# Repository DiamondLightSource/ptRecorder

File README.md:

# ptRecorder
Pressure and Temperature recorder created by Daniel Brennand and comissioned by DLS Vacuum Dept.

### DLS Contacts

- Hugo Shiers
- Giles Knap

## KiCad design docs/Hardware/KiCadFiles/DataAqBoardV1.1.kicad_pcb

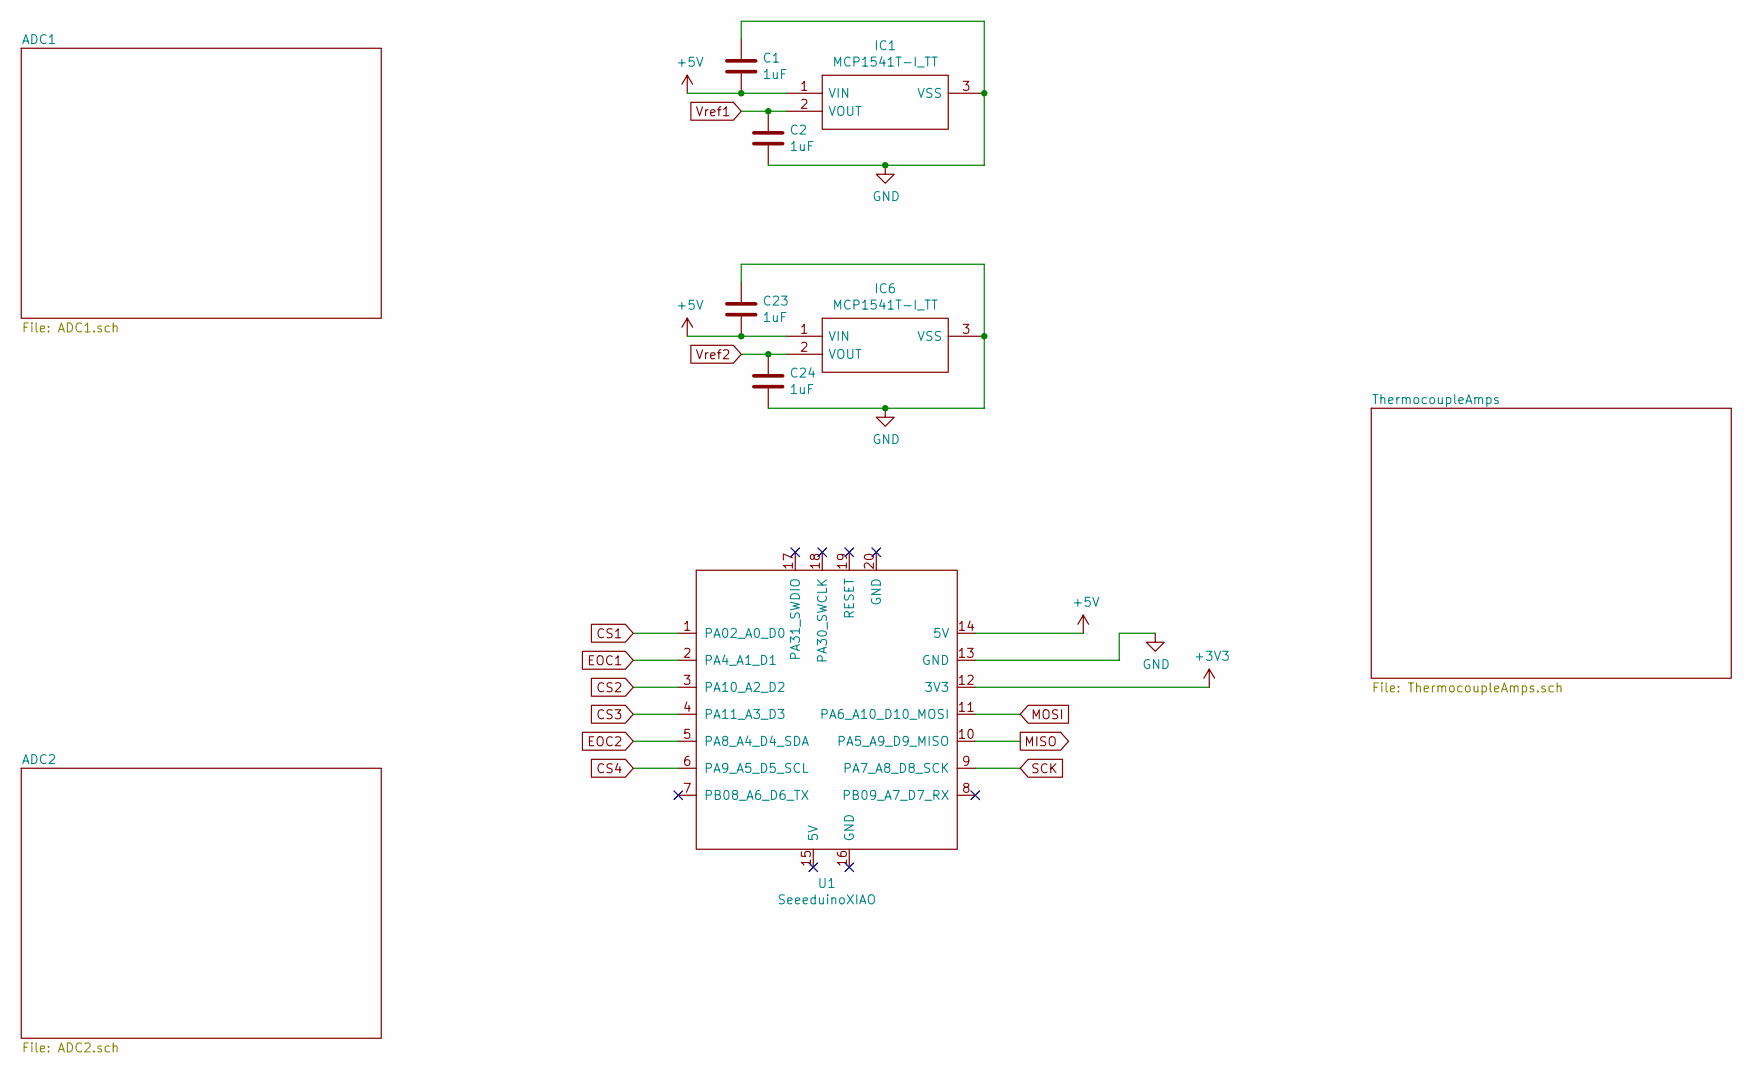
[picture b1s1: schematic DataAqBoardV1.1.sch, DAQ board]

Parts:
C1, C2, C23, C24: 1uF; C_0201_0603Metric
IC1, IC6: MCP1541T-I_TT; SOT96P237X112-3N; Manufacturer_Part_Number MCP1541T-I/TT
U1: SeeeduinoXIAO; Seeeduino XIAO-MOUDLE14P-2.54-21X17.8MM

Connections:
+3V3: U1.12 (3V3); also elsewhere on the board
+5V: C1.2, C23.2, IC1.1 (VIN), IC6.1 (VIN), U1.14 (5V); also elsewhere on the board
CS1: U1.1 (PA02_A0_D0); also elsewhere on the board
CS2: U1.3 (PA10_A2_D2); also elsewhere on the board
CS3: U1.4 (PA11_A3_D3); also elsewhere on the board
CS4: U1.6 (PA9_A5_D5_SCL); also elsewhere on the board
EOC1: U1.2 (PA4_A1_D1); also elsewhere on the board
EOC2: U1.5 (PA8_A4_D4_SDA); also elsewhere on the board
GND: C1.1, C2.2, C23.1, C24.2, IC1.3 (VSS), IC6.3 (VSS), U1.13 (GND); also elsewhere on the board
MISO: U1.10 (PA5_A9_D9_MISO); also elsewhere on the board
MOSI: U1.11 (PA6_A10_D10_MOSI); also elsewhere on the board
SCK: U1.9 (PA7_A8_D8_SCK); also elsewhere on the board
Vref1: C2.1, IC1.2 (VOUT); also elsewhere on the board
Vref2: C24.1, IC6.2 (VOUT); also elsewhere on the board

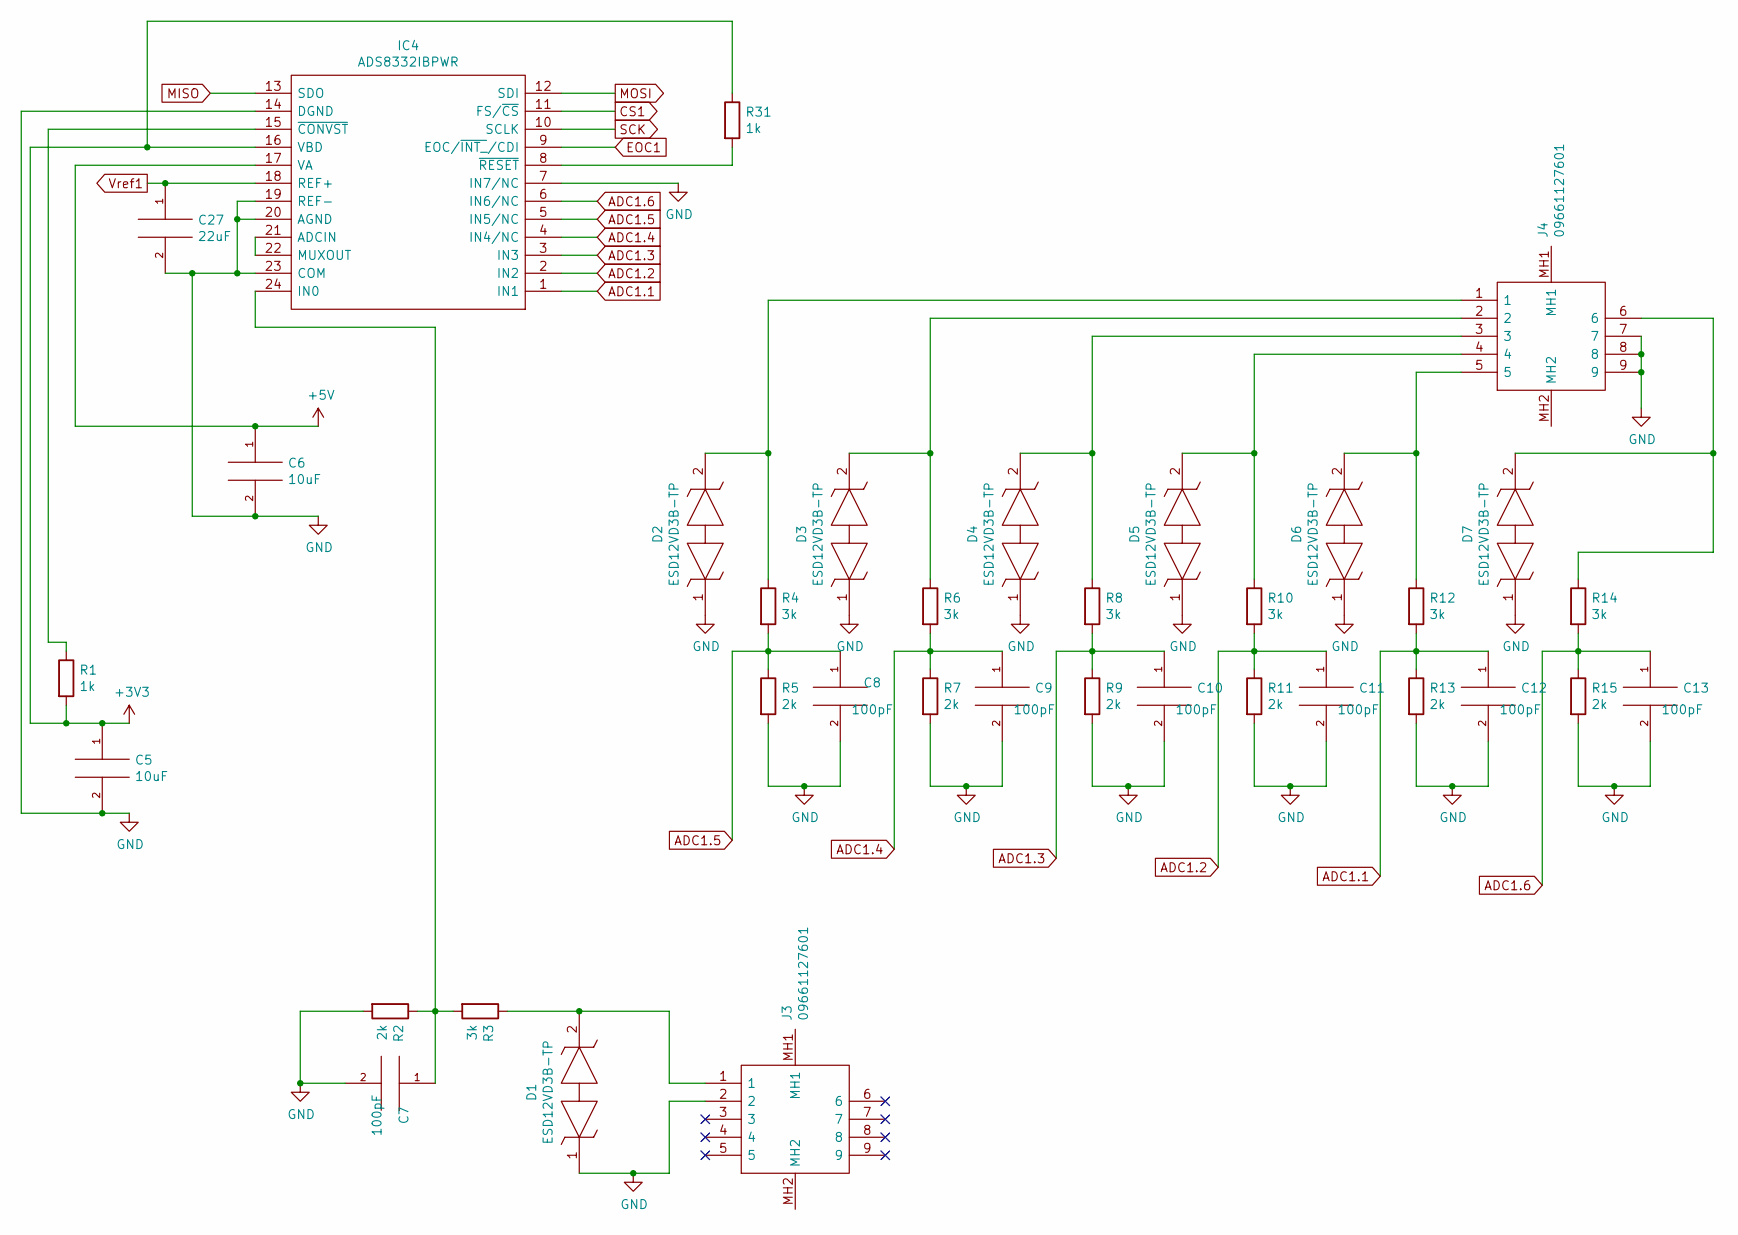
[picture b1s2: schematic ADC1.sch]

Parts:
C5, C6: 10uF; C_0201_0603Metric
C7, C8, C9, C10, C11, C12, C13: 100pF; C_0201_0603Metric
C27: 22uF; C_0201_0603Metric
D1, D2, D3, D4, D5, D6, D7: ESD12VD3B-TP; SOD2512X115N; Manufacturer_Part_Number ESD12VD3B-TP
IC4: ADS8332IBPWR; SOP65P640X120-24N; Manufacturer_Part_Number ADS8332IBPWR
J3, J4: 09661127601; 09661126600; Manufacturer_Part_Number 09661127601
R1, R31: 1k; R_0201_0603Metric
R2, R5, R7, R9, R11, R13, R15: 2k; R_0201_0603Metric
R3, R4, R6, R8, R10, R12, R14: 3k; R_0201_0603Metric

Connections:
+3V3: C5.1, IC4.16 (VBD), R1.2, R31.1; also elsewhere on the board
+5V: C6.1, IC4.17 (VA); also elsewhere on the board
ADC1.1: C12.1, IC4.1 (IN1), R12.2, R13.1
ADC1.2: C11.1, IC4.2 (IN2), R10.2, R11.1
ADC1.3: C10.1, IC4.3 (IN3), R8.2, R9.1
ADC1.4: C9.1, IC4.4 (IN4/NC), R6.2, R7.1
ADC1.5: C8.1, IC4.5 (IN5/NC), R4.2, R5.1
ADC1.6: C13.1, IC4.6 (IN6/NC), R14.2, R15.1
CS1: IC4.11 (FS/~CS); also elsewhere on the board
EOC1: IC4.9 (EOC/~INT_~/CDI); also elsewhere on the board
GND: C5.2, C6.2, C7.2, C8.2, C9.2, C10.2, C11.2, C12.2, C13.2, C27.2, D1.1, D2.1, D3.1, D4.1, D5.1, D6.1, D7.1, IC4.7 (IN7/NC), IC4.14 (DGND), IC4.19 (REF-), IC4.20 (AGND), IC4.23 (COM), J3.2, J4.7, J4.8, J4.9, R2.2, R5.2, R7.2, R9.2, R11.2, R13.2, R15.2; also elsewhere on the board
MISO: IC4.13 (SDO); also elsewhere on the board
MOSI: IC4.12 (SDI); also elsewhere on the board
unnamed: C7.1, IC4.24 (IN0), R2.1, R3.2
unnamed: D1.2, J3.1, R3.1
unnamed: D2.2, J4.1, R4.1
unnamed: D3.2, J4.2, R6.1
unnamed: D4.2, J4.3, R8.1
unnamed: D5.2, J4.4, R10.1
unnamed: D6.2, J4.5, R12.1
unnamed: D7.2, J4.6, R14.1
unnamed: IC4.8 (~RESET), R31.2
unnamed: IC4.15 (~CONVST), R1.1
unnamed: IC4.21 (ADCIN), IC4.22 (MUXOUT)
SCK: IC4.10 (SCLK); also elsewhere on the board
Vref1: C27.1, IC4.18 (REF+); also elsewhere on the board

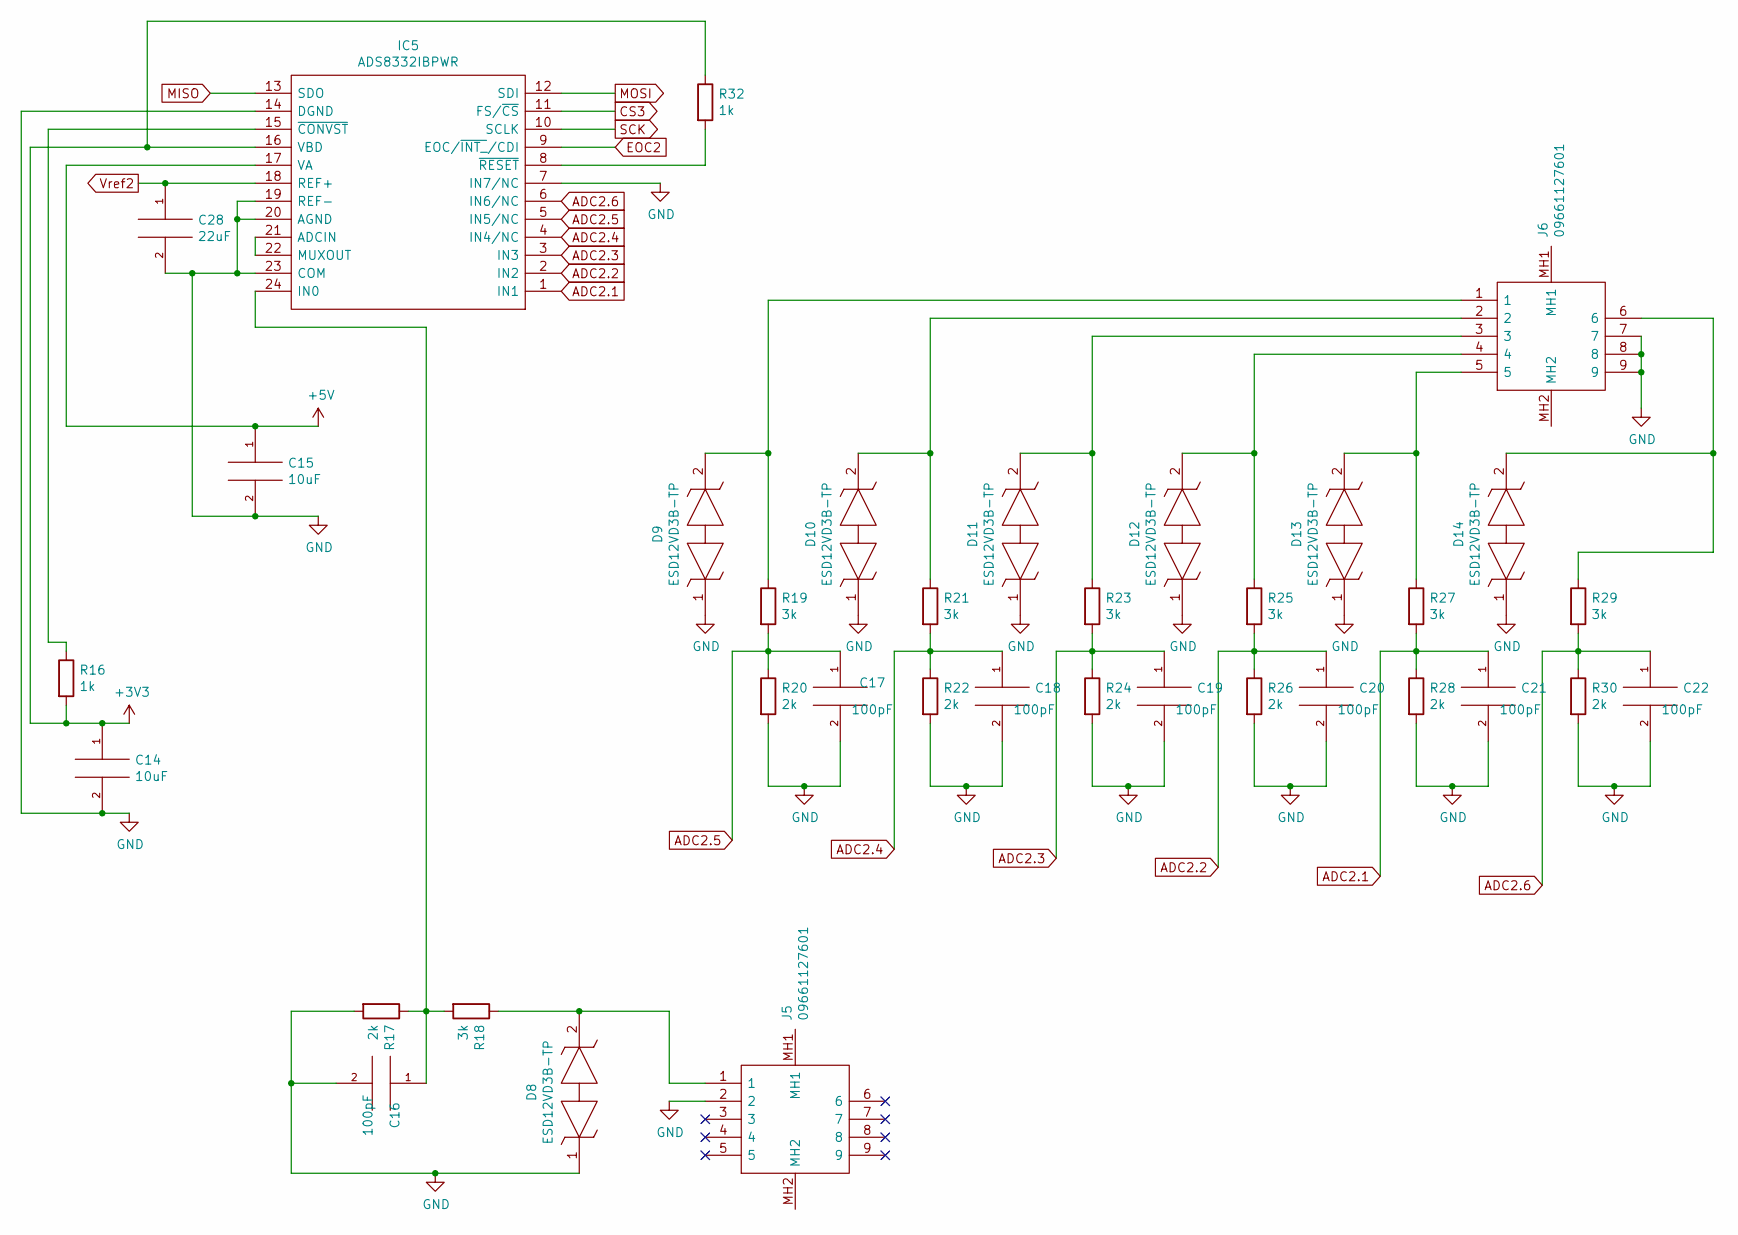
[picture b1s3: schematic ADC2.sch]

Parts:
C14, C15: 10uF; C_0201_0603Metric
C16, C17, C18, C19, C20, C21, C22: 100pF; C_0201_0603Metric
C28: 22uF; C_0201_0603Metric
D8, D9, D10, D11, D12, D13, D14: ESD12VD3B-TP; SOD2512X115N; Manufacturer_Part_Number ESD12VD3B-TP
IC5: ADS8332IBPWR; SOP65P640X120-24N; Manufacturer_Part_Number ADS8332IBPWR
J5, J6: 09661127601; 09661126600; Manufacturer_Part_Number 09661127601
R16, R32: 1k; R_0201_0603Metric
R17, R20, R22, R24, R26, R28, R30: 2k; R_0201_0603Metric
R18, R19, R21, R23, R25, R27, R29: 3k; R_0201_0603Metric

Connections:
+3V3: C14.1, IC5.16 (VBD), R16.2, R32.1; also elsewhere on the board
+5V: C15.1, IC5.17 (VA); also elsewhere on the board
ADC2.1: C21.1, IC5.1 (IN1), R27.2, R28.1
ADC2.2: C20.1, IC5.2 (IN2), R25.2, R26.1
ADC2.3: C19.1, IC5.3 (IN3), R23.2, R24.1
ADC2.4: C18.1, IC5.4 (IN4/NC), R21.2, R22.1
ADC2.5: C17.1, IC5.5 (IN5/NC), R19.2, R20.1
ADC2.6: C22.1, IC5.6 (IN6/NC), R29.2, R30.1
CS3: IC5.11 (FS/~CS); also elsewhere on the board
EOC2: IC5.9 (EOC/~INT_~/CDI); also elsewhere on the board
GND: C14.2, C15.2, C16.2, C17.2, C18.2, C19.2, C20.2, C21.2, C22.2, C28.2, D8.1, D9.1, D10.1, D11.1, D12.1, D13.1, D14.1, IC5.7 (IN7/NC), IC5.14 (DGND), IC5.19 (REF-), IC5.20 (AGND), IC5.23 (COM), J5.2, J6.7, J6.8, J6.9, R17.2, R20.2, R22.2, R24.2, R26.2, R28.2, R30.2; also elsewhere on the board
MISO: IC5.13 (SDO); also elsewhere on the board
MOSI: IC5.12 (SDI); also elsewhere on the board
unnamed: C16.1, IC5.24 (IN0), R17.1, R18.2
unnamed: D8.2, J5.1, R18.1
unnamed: D9.2, J6.1, R19.1
unnamed: D10.2, J6.2, R21.1
unnamed: D11.2, J6.3, R23.1
unnamed: D12.2, J6.4, R25.1
unnamed: D13.2, J6.5, R27.1
unnamed: D14.2, J6.6, R29.1
unnamed: IC5.8 (~RESET), R32.2
unnamed: IC5.15 (~CONVST), R16.1
unnamed: IC5.21 (ADCIN), IC5.22 (MUXOUT)
SCK: IC5.10 (SCLK); also elsewhere on the board
Vref2: C28.1, IC5.18 (REF+); also elsewhere on the board

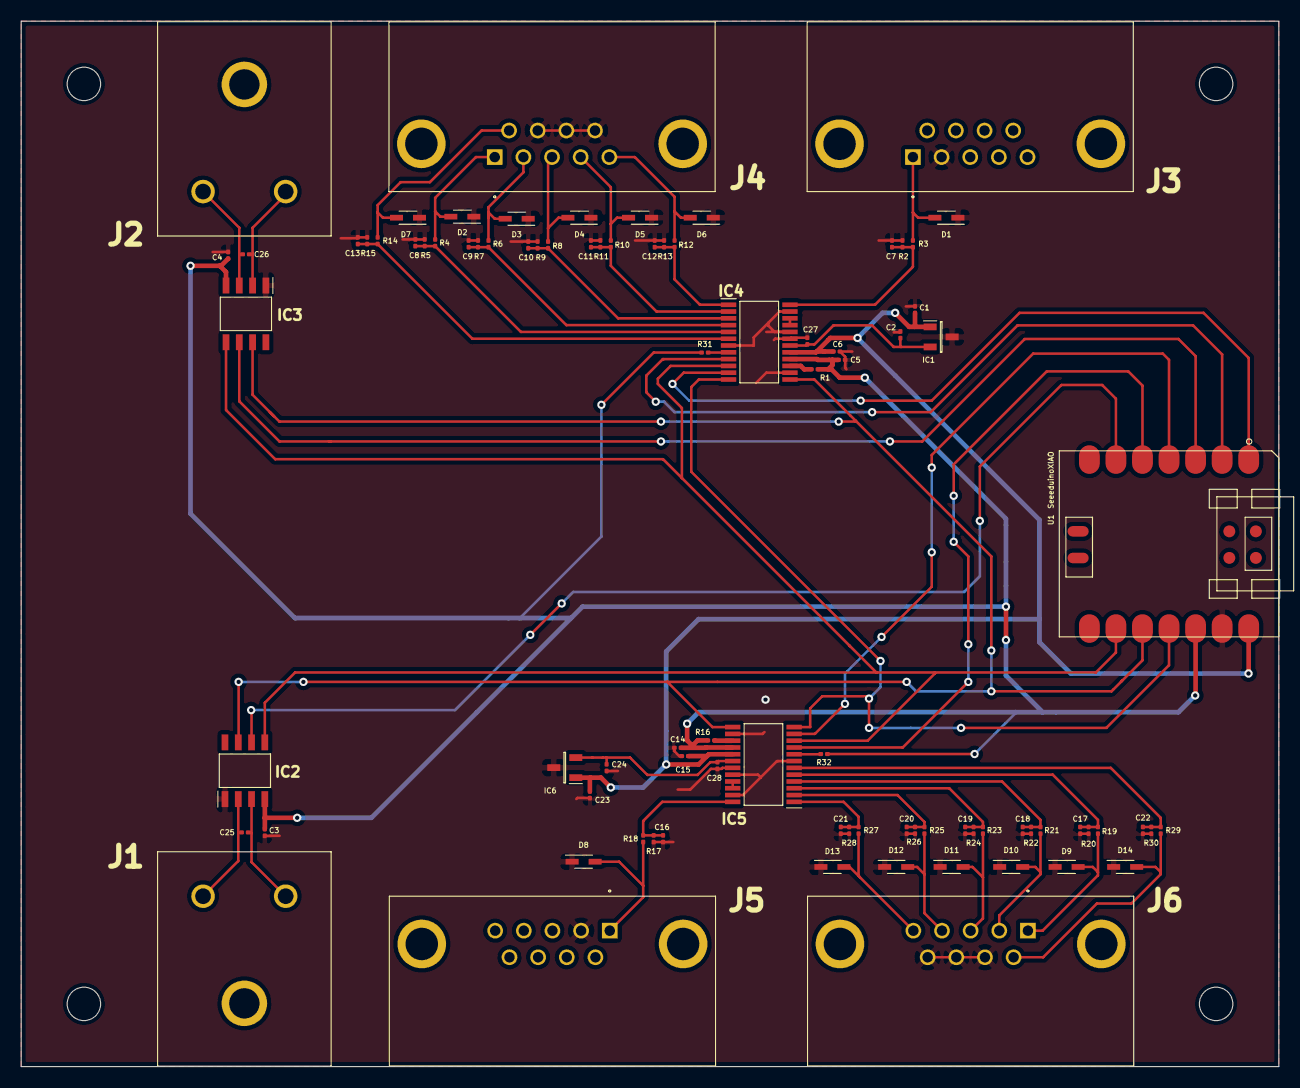
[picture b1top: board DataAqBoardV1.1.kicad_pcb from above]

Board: 2 copper layers, 120.3 x 100.0 mm, 87 parts (0 on the bottom side), 52 nets.

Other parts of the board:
C3, C4: 0.1uF; C_0201_0603Metric
C25, C26: 0.01uF; C_0201_0603Metric
IC2, IC3: MAX31855KASA+; SOIC127P600X175-8N
J1, J2: 3817564

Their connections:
+3V3: C3.1, C4.1, IC2.4, IC3.4; also elsewhere on the board
CS2: IC3.6; also elsewhere on the board
CS4: IC2.6; also elsewhere on the board
GND: C3.2, C4.2, IC2.1, IC3.1; also elsewhere on the board
MISO: IC2.7, IC3.7; also elsewhere on the board
unnamed: C25.1, IC2.2, J1.1
unnamed: C25.2, IC2.3, J1.2
unnamed: C26.1, IC3.2, J2.1
unnamed: C26.2, IC3.3, J2.2
SCK: IC2.5, IC3.5; also elsewhere on the board

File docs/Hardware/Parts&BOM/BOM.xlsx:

| Part Name | MFR Part number | Quantity | Designator | Value
 | ADC | ADS8332IBPWR | 2 | IC4, IC5
 | Reference IC | MCP1541T-I/TT | 2 | IC1, IC6
 | 9 Pin connector | 9661127601 | 4 | J3, J4, J5, J5
 | Thermocouple Amp | MAX31855KASA+ | 2 | IC2, IC3
 | Thermocouple Conector | 381-7564 | 2 | J1, J2
 | Zener Diode | ESD12VD3B-TP | 14 | D1, D2, D3, D4, D5, D6, D7, D8, D9, D10, D11, D12, D13, D14
 | Resistor (1k) | ERJ-3GEYJ102V | 4 | R1, R16, R31, R32 | 1k
 | Resistor (2k) | RMCF0402FT2K00 | 14 | R2, R5, R7, R9, R11, R13, R15, R17, R20, R22, R24, R26, R28, R30 | 2k
 | Resistor (3k) | ERJ-6GEYJ302V | 14 | R3, R4, R6, R8, R10, R12, R14, R18, R19, R21, R23, R25, R27, R29 | 3k
 | Capacitor (0.1uF) | C0402C104K4PACTU | 2 | C3, C4 | 0.1uF
 | Capacitor (100pF) | C0402C101K5RAC7867 | 14 | C7, C8, C9, C10, C11, C12, C13, C16, C17, C18, C19, C20, C21, C22 | 100pF
 | Capacitor (10uF) | CL21A106KPCLQNC | 4 | C5, C6, C14, C15 | 10uF
 | Capacitor (1uF) | C0603C105K8RACTU | 4 | C1, C2, C23, C24 | 1uF
 | Capacitor (0.01uF) | CL05B103KB5VPJC | 2 | C25, C26 | 0.01uF
 | Capacitor (22uF) | CL21X226MRQNNNE | 2 | C27, C28 | 22uF
 | Seeduino Xiao | 1E4-D57-5A2 | 1 | U1

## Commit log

2021-11-04 initial version
2021-11-04 remove temp docx files
2021-12-17 Fixed several ui label mistakes and fixed conversion errors
    Several ui labels for the ports were mislabeled and have now been corrected.
    Added a tag to the end of each of the channel labels denoting the port they are connected to (I.e. P1 for port 1 etc)
    Added a new conversion (Conversion 0) to represent simply keeping the raw voltages and updated where the data is converted and the desired conversion selected to incorperate this now.
2021-12-17 Forgot one port label
    Forgot a port label in the ui
2022-02-02 Fixed thermo voltage conversion, fullscreen bug
    Fixed the thermocouple voltage conversion,
    Set fullscreen hopefully stopping the gui text crash
    Changed Dev button to exit button
